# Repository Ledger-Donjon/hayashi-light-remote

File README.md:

# Hayashi-light-remote

An Open-Source and Open-Hardware USB dongle for controlling Hayashi light source
LA-150CE remotely. It should also be compatible with LA-150UE, LA-100IR and
LA-150FBU, but this has not been tested (any feedback is welcome).

The halogen lamp can be turned on and off, and its intensity can be adjusted
from the software.

# Python API

Once the dongle is connected to the lamp and the computer, the provided Python3
library can be used to communicate with the dongle and take control of the lamp:

```python
import hyshlr

device = hyshlr.HyshLR()
device.lamp = True
device.intensity = 0.5
```

# External documentation

[Manufacturer documentation with remote connector interface specification](http://www.korin-hayashi.com.cn/uploadfile/2018/1030/20181030095820716.pdf)

## Licensing

This project is licensed under the GNU Lesser General Public Licence version 3
(LGPLv3). See COPYING and COPYING.LESSER for license details.

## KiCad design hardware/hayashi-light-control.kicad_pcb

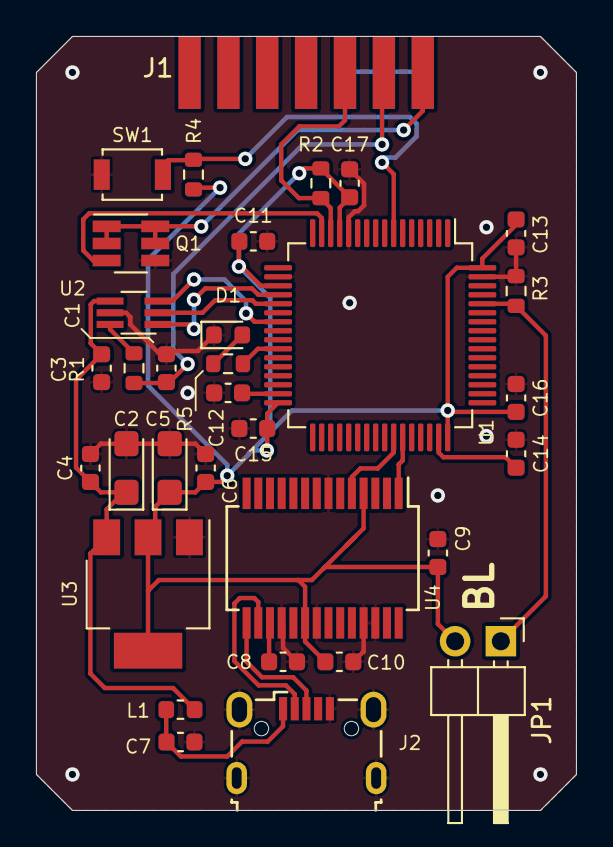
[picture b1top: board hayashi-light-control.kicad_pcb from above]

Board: 2 copper layers, 30.0 x 43.0 mm, 34 parts (1 on the bottom side), 23 nets.

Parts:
C1, C12, C14: 2.2µ; C_0603_1608Metric
C2, C5: 10µ; CP_EIA-3216-10_Kemet-I
C3, C4, C6, C7, C8, C9, C10, C11, C13, C15, C16, C17: 100n; C_0603_1608Metric
D1: Green; D_0603_1608Metric
J1: Conn_02x07_Top_Bottom; Amphenol_5710140
J2: USB_B_Micro; USB_Micro-B_Wuerth_629105150521
JP1: Jumper_2_Open; PinHeader_1x02_P2.54mm_Horizontal
L1: Ferrite_Bead_Small; L_0603_1608Metric
LOGO1: DONJON LOGO; donjon-2000
Q1: STT6N3LLH6; SOT-23-6_Handsoldering
R1: R_Small; R_0603_1608Metric
R2: 10K; R_0603_1608Metric
R3, R4: 10k; R_0603_1608Metric
R5: 330; R_0603_1608Metric
SW1: RESET; SW_SPST_B3U-1000P
U1: STM32F205RET6; LQFP-64_10x10mm_P0.5mm
U2: AD5621B; SOT-363_SC-70-6_Handsoldering
U3: LD1117S33TR_SOT223; SOT-223-3_TabPin2
U4: FT232RL; SSOP-28_5.3x10.2mm_P0.65mm

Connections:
+3V3: C5.1, C6.1, C9.2, C10.2, C11.1, C13.1, C15.1, C16.1, C17.1, JP1.2 (B), R2.1, R4.1, U1.13 (VDDA), U1.19 (VDD), U1.32 (VDD), U1.48 (VDD), U1.64 (VDD), U3.2 (VO), U4.4 (VCCIO), U4.20 (VCC)
/CON1: J1.1, Q1.1, Q1.2, Q1.5, Q1.6
/CON2: C1.1, J1.2, R1.1
/CON3: J1.3, R2.2, U1.14 (PA0)
/LAMP_ON_OFF: Q1.3, U1.15 (PA1)
/SPI_MOSI: U1.23 (PA7), U2.3 (SDIN)
/SPI_NSS: U1.20 (PA4), U2.1 (~SYNC)
/SPI_SCK: U1.21 (PA5), U2.2 (SCLK)
/TX: U1.43 (PA10), U4.1 (TXD)
/TX_1: U1.42 (PA9), U4.5 (RXD)
GND: C1.2, C2.2, C3.2, C4.2, C5.2, C6.2, C7.1, C8.2, C9.1, C10.1, C11.2, C12.2, C13.2, C14.2, C15.2, C16.2, C17.2, D1.1 (K), J1.8, J1.9, J1.10, J2.5 (GND), J2.6 (Shield), Q1.4, R3.2, SW1.1, U1.12 (VSSA), U1.18 (VSS), U1.63 (VSS), U2.5 (GND), U3.1 (GND), U4.7 (GND), U4.18 (GND), U4.21 (GND), U4.25 (AGND), U4.26 (TEST)
unnamed: C7.2, J2.1 (VBUS), L1.1
unnamed: C8.1, U4.17 (3V3OUT)
unnamed: C12.1, U1.31 (VCAP_1)
unnamed: C14.1, U1.47 (VCAP_2)
unnamed: D1.2 (A), R5.2
unnamed: J2.2 (D-), U4.16 (USBD-)
unnamed: J2.3 (D+), U4.15 (USBD+)
unnamed: JP1.1 (A), R3.1, U1.60 (BOOT0)
unnamed: R1.2, U2.6 (VOUT)
unnamed: R4.2, SW1.2, U1.7 (NRST)
unnamed: R5.1, U1.26 (PB0)
VBUS: C2.1, C3.1, C4.1, L1.2, U2.4 (VDD), U3.3 (VI)

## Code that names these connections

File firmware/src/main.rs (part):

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        w.usart1en().set_bit()
        .spi1en().set_bit()
    });
    // PA0: LAMP_BURNOUT
    // PA1: LAMP_ON_OFF
    // PA4: SPI_NSS
    // PA5: SPI_SCK
    // PA6: SPI_MISO (not connected)
    // PA7: SPI_MOSI
    // PA9: USART1 TX
    // PA10: USART1 RX
    // PB0: LED
    // Enable clock for PORT A, and PORT B peripherals.
    peripherals.RCC.ahb1enr.write(
        |w| { w.gpioaen().set_bit().gpioben().set_bit() } );
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        .ospeedr5().very_high_speed()
        .ospeedr7().very_high_speed()
    });
    gpioa.odr.modify(|_, w| { w.odr4().set_bit() }); // SPI_NSS high by default
    gpioa.afrl.write(|w| { w.afrl5().af5().afrl7().af5() });
    gpioa.afrh.write(|w| { w.afrh9().af7().afrh10().af7() });
    peripherals.GPIOB.moder.modify(|_, w| { w.moder0().output() });
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
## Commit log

2020-12-10 Initial release
2020-12-11 Fixed dongle detection
2020-12-11 Renammed property power to intensity
2020-12-11 Appropriate exceptions for connection errors
2020-12-11 Added current setting readout
2020-12-11 Removed debug print
2021-10-05 Fixed bug in disconnect method
2022-06-07 Lamp burnout indicator
2022-06-07 Updated heapless due to security vulnerability
2022-06-07 Updated .gitignore to include Cargo.lock
2025-01-24 From setup.py to pyproject.toml
2025-03-03 Update the pyproject.toml file to remove deprectated configuration
2026-03-30 Add GitHub Actions workflow for linting and type checking
    - Introduced a new GitHub Actions workflow in `python.yml` to automate linting with Ruff and type checking with MyPy on push and pull request events.
    - Updated `pyproject.toml` to include build system configuration and specify Python version requirements.
    - Refactored the `HyshLR` class and related error handling into separate files for better organization.
    - Added unit tests for the `HyshLR` class to ensure functionality and error handling.
    - Bumped version to 1.1.0 to reflect changes and improvements.
2026-03-30 Refactor tests for HyshLR to improve type hints and functionality
    - Updated the `hyshlr_real` fixture to include a return type hint.
    - Enhanced type hints for test functions to specify the expected type of `hyshlr_real`.
    - Consolidated and renamed tests for clarity, changing `test_real_set_led` to `test_lamp_state` and adding `test_intensity` for intensity adjustments.
    - Removed redundant tests related to state retrieval and relay toggling to streamline the test suite.
2026-03-31 Update GitHub Actions workflow and refine test cases for HyshLR
    - Upgraded the `setup-python` action to version 6 in the GitHub Actions workflow.
    - Changed the pip install command to specify the `api` directory for dependencies.
    - Modified the `hyshlr_real` fixture by removing the `connect` call to streamline setup.
    - Increased sleep duration in `test_lamp_state` for stability.
    - Enhanced `test_intensity` to test a broader range of intensity values with improved assertions.

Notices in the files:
firmware/src/main.rs:
hayashi-light-remote is free software: you can redistribute it and/or modify
it under the terms of the GNU Lesser General Public License as published by
the Free Software Foundation, either version 3 of the License, or
(at your option) any later version.
Copyright 2020 Ledger SAS, written by Olivier Hériveaux
hardware/hayashi-light-control.kicad_pcb:
Licensed under LGPLv3
